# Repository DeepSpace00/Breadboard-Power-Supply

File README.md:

# Breadboard-Power-Supply
Duel power supply for breadboard power rails

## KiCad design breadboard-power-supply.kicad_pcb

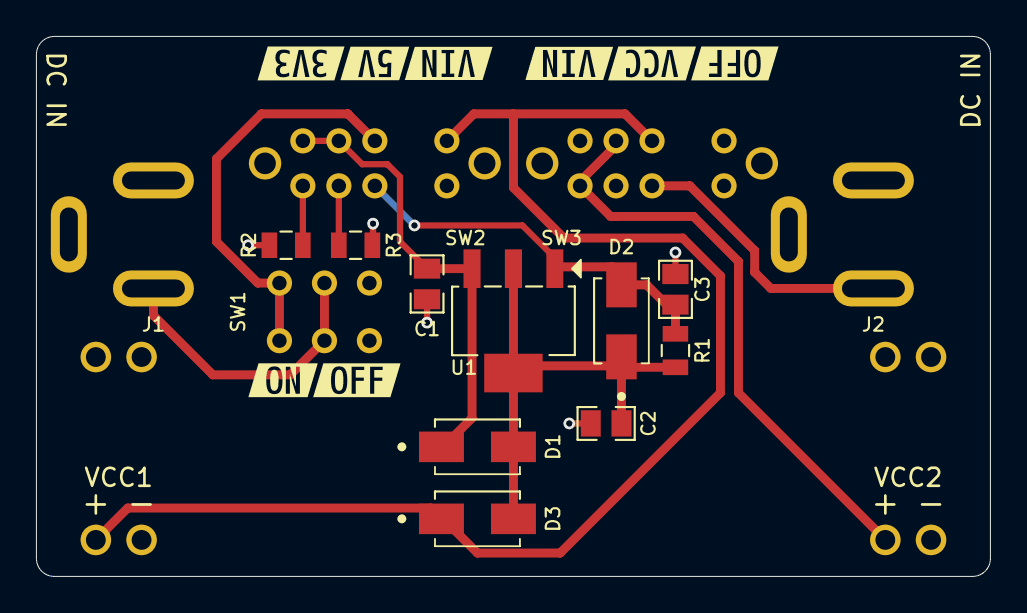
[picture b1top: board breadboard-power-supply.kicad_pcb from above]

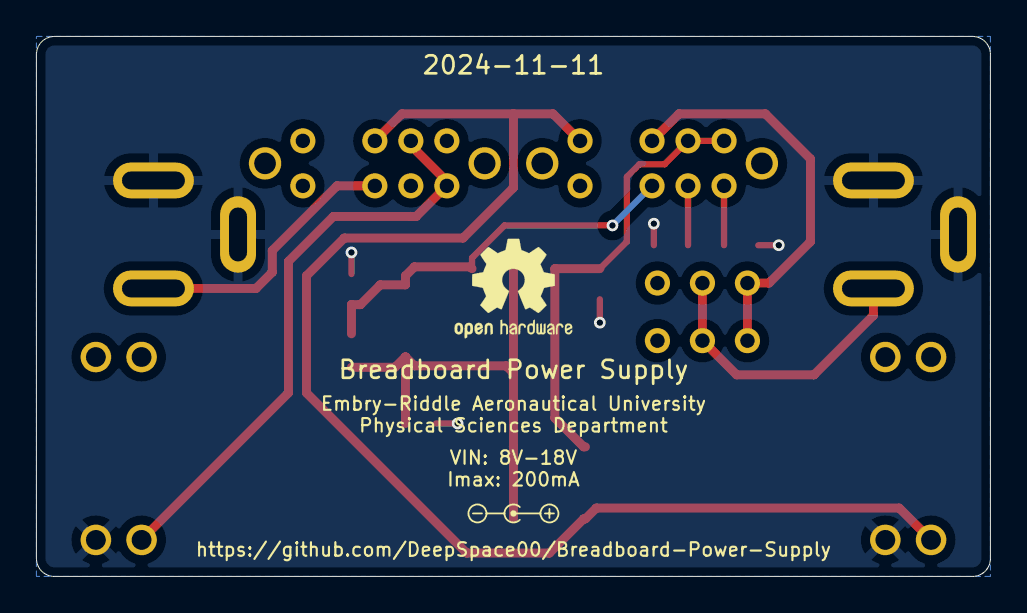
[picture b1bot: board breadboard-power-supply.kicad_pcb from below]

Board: 2 copper layers, 53.0 x 30.0 mm, 27 parts (4 on the bottom side), 11 nets.

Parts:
C1: 100nF; CAPC200X125X88L50N
C2: 1uF; CAPC200X125X88L50N
C3: 10uF; CAPC200X125X88L50N
D1, D2: ES1B-13-F; SMA
D3: B140-13-F; SMA
J1, J2: PJ-002A
J3, J4, J5, J6: TSW-102-07-F-S; conn_01x02_254
R1: 280R; RESC200X125X60L35_35N
R2: 510R; RESC200X125X60L35_35N
R3: 887R; RESC200X125X60L35_35N
SW1: EG1271; EG-1271
SW2, SW3: EG2315; EG-2315
U1: LM317M; SOT223-4
kibuzzard-66FD9C27: G***; kibuzzard-66FD9C27
kibuzzard-66FD9C35: G***; kibuzzard-66FD9C35
kibuzzard-66FD9C43: G***; kibuzzard-66FD9C43
kibuzzard-66FD9CA2: G***; kibuzzard-66FD9CA2
kibuzzard-66FD9CB0: G***; kibuzzard-66FD9CB0
kibuzzard-66FD9CBB: G***; kibuzzard-66FD9CBB
kibuzzard-66FD9D64: G***; kibuzzard-66FD9D64
kibuzzard-66FD9D69: G***; kibuzzard-66FD9D69

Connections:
/ADJ: C3.1, D2.1, R1.2, SW2.6, U1.1 (Adj)
/VIN1: SW1.1, SW1.4, SW2.2
GND: C1.2, C2.2, C3.2, J1.2, J1.3, J2.2, J2.3, J4.2, J6.2, R2.2, R3.2
unnamed: C2.1, D1.1, D2.2, D3.1, R1.1, U1.2 (OUT), U1.4 (OUT)
unnamed: J1.1, SW1.2, SW1.5
unnamed: J2.1, SW3.6
unnamed: R2.1, SW2.8
unnamed: R3.1, SW2.7
unnamed: C1.1, D1.2, SW2.3, SW2.4, U1.3 (IN)
VCC1: D3.2, J4.1, SW2.1, SW3.2
VCC2: J6.1, SW3.3, SW3.8

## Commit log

2024-09-25 added gitignore
2024-09-25 added CERN OHL-P license
2024-09-25 added VS Code workspace file
2024-09-25 created PCB files
2024-09-25 added component datasheets
2024-09-25 lock file
2024-09-25 most of sch done
2024-09-25 added lock file to gitignore
2024-09-29 removed obsolete datasheets
2024-09-29 added new datasheets for components
2024-09-29 added 3D models for components
2024-09-29 added footprints to project library
2024-09-29 added symbols to project library
2024-09-29 fixed switches in schematic
2024-09-29 pcb layout
2024-10-02 moved libraries
2024-10-02 reassigned parts from libraries
2024-10-02 export gerbers and BOM
2024-10-02 updated quote and moved stencil gerbers up a directory
2024-10-02 exported board images
2024-10-02 fixed SMA courtyard
2024-10-02 modified chip outline on fab and drawing layers
2024-10-02 cleaned up files and scrubbed meta data
2024-10-02 export schematic
2024-10-02 SPICE sim for LM317
2024-10-03 added purchase request form and updated gerbers
2024-10-03 Rearranged manufacturing and assembly file structure
2024-10-07 Fixed purchase request form
2024-10-07 exported layout drawings
2024-10-07 added workspace and ibom config file to gitignore
2024-10-07 created ibom
2024-10-07 added banana to barrel plug adapter to purchase request form
2024-10-14 replaced drawing sheet file
2024-10-14 enlarged silk screen text on the bottom and added knockout to VIN and Imax
2024-10-14 exported gerbers
2024-10-14 updated purchase form
2024-10-14 plotted gerbers
2024-10-14 fixed date on board
2024-11-11 fixed diodes rotation and fixed voltage divider
2024-11-11 deleted autosave file
2024-11-11 fixed sheet date and equation
2024-11-11 fixed sheet name and equation
2024-12-15 STEP export path
2024-12-15 regenerated IBOM
2024-12-15 creaded gitignore for FreeCAD files
2024-12-15 FreeCAD generated model for board
2024-12-15 kicad exported STEP file
2024-12-15 jig for holding board while soldering through hole components
2024-12-15 stl for 3D printing
2024-12-15 assembly file for fit testing
